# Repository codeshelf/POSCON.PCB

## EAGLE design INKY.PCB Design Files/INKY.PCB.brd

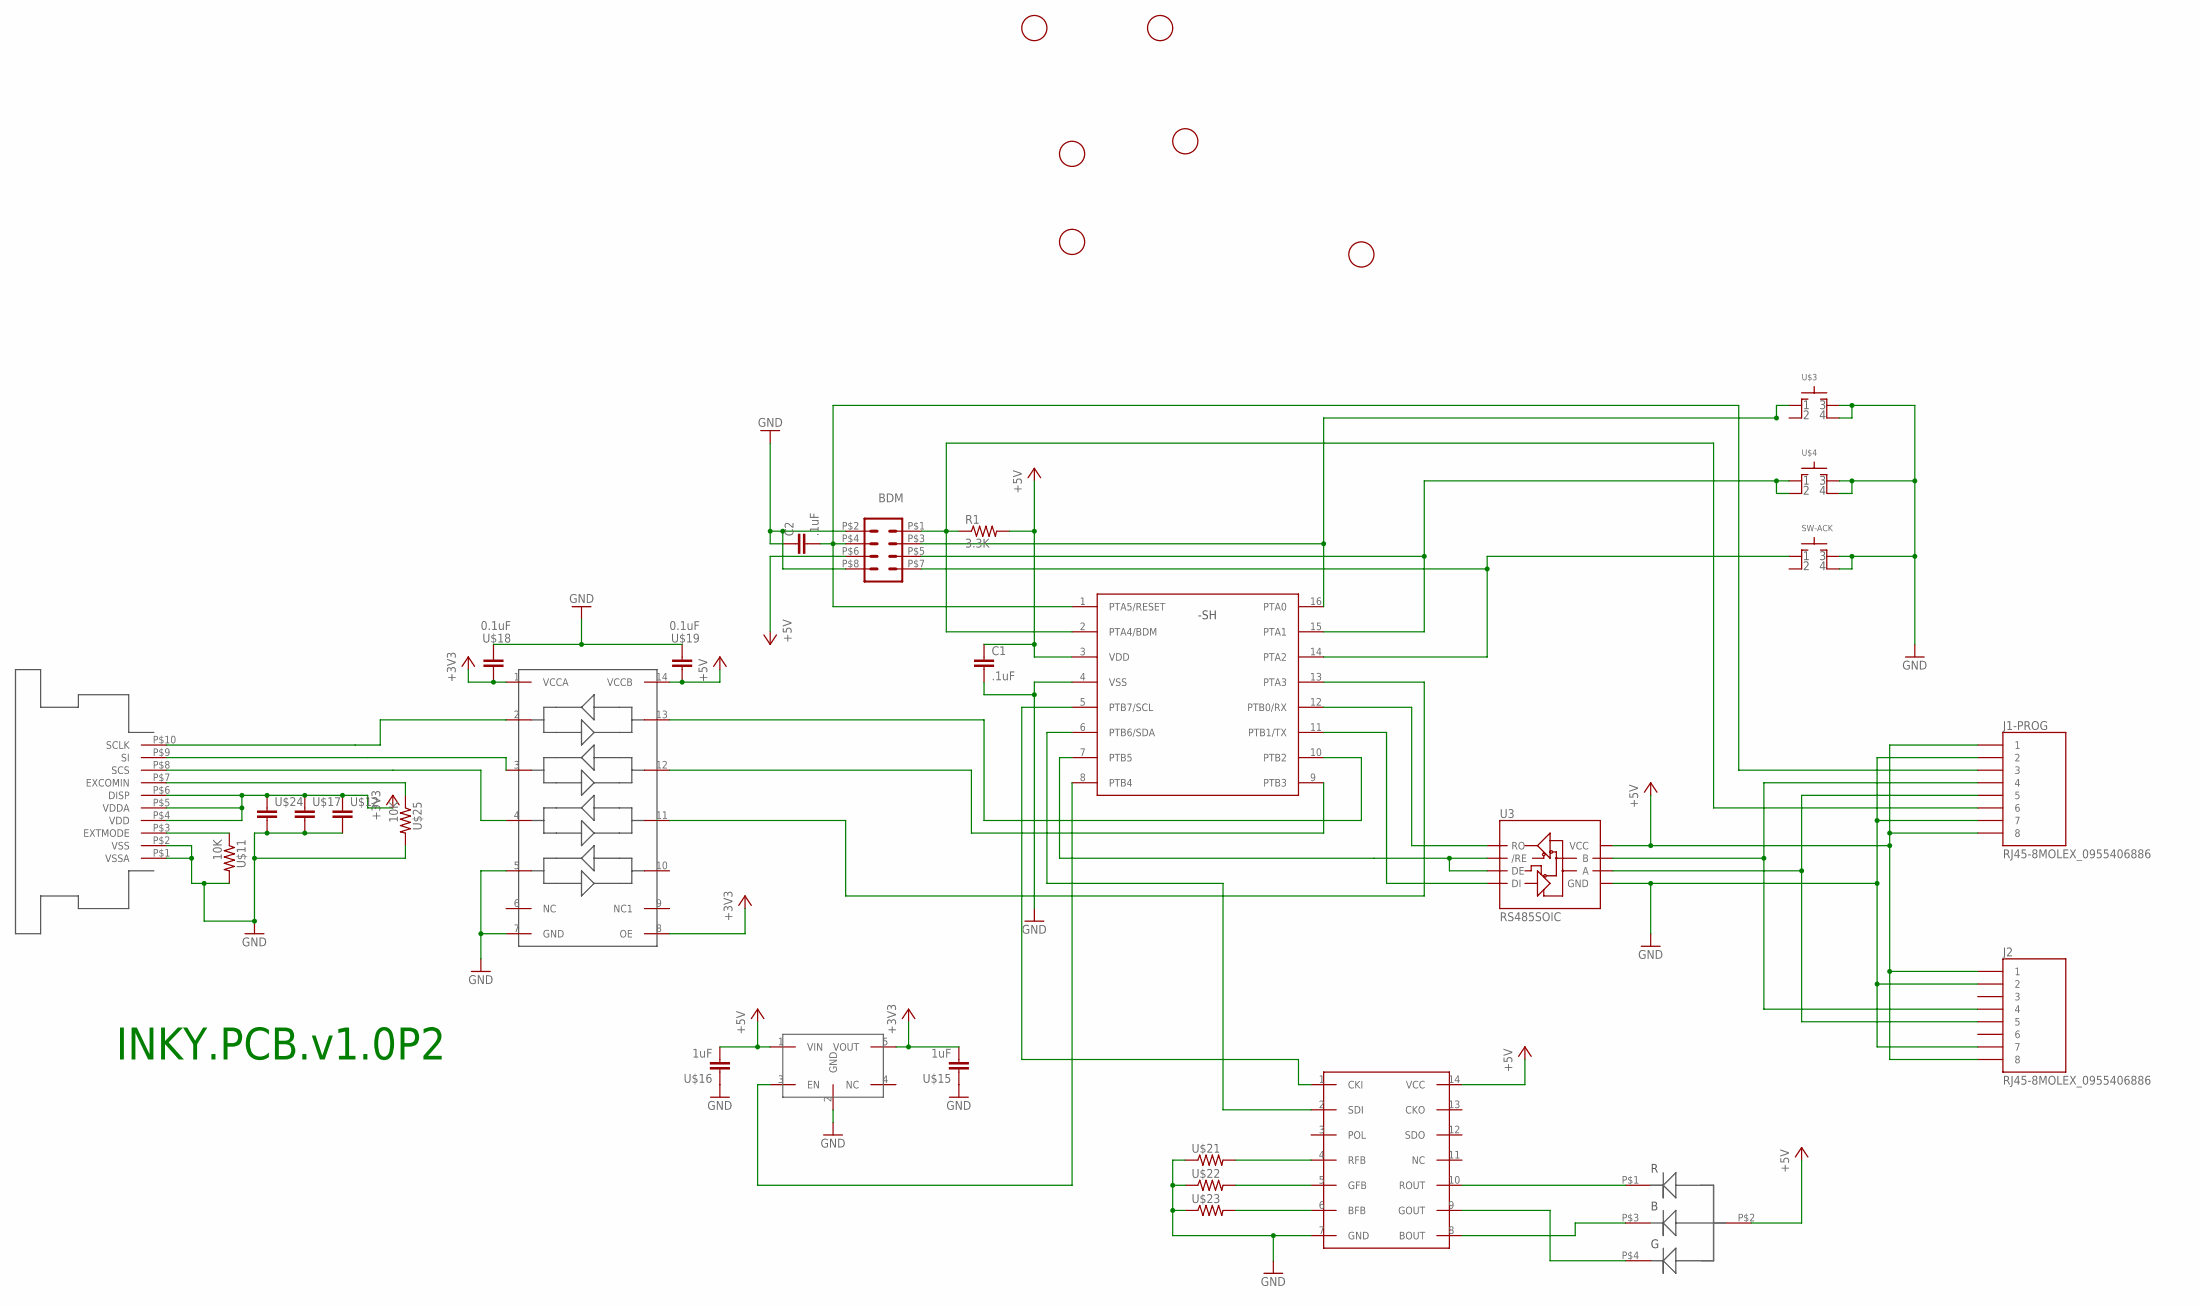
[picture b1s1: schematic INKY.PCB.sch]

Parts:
BDM: TP2X4SMD; SMD4X2
C1, C2: .1uF; C0805
J1-PROG, J2: RJ45-8MOLEX_0955406886; RJ45_GUIDE
R1: 3.3K; RF-C0805
SW-ACK: SWITCH-TACTILE-5E/5GSH9; SWITCH_TACTILE-5E/5GSH9
U1: MC9S08SH8CTG; TSSOP16
U3: RS485SOIC; SO08
U$1, U$2, U$6, U$7, U$8, U$9: FIDUCIAL; FIDUCIAL_1MM
U$3, U$4: SWITCH-TACTILE; ESWITCH-TL3301PF
U$5: WS2801; SO14
U$10: 52745-1097; FPC
U$11, U$25: 10K; RF-C0805
U$12, U$17, U$24: RF-C0805; C0805
U$13: AAT3221IGV-3.3-T1; SOT23-5
U$14: TXB0104; PW_R-PDSO-G14
U$15, U$16: 1uF; C0805
U$18, U$19: 0.1uF; C0805
U$20: RGLBED; PLCC4_SMALL
U$21, U$22, U$23: RF-R0805; RF-C0805

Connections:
485N: J1-PROG.P$4 (4), J2.P$4 (4), U3.7 (B)
485P: J1-PROG.P$5 (5), J2.P$5 (5), U3.6 (A)
+5V: BDM.P$6 (6), C1.1, J1-PROG.P$1 (1), J1-PROG.P$8 (8), J2.P$1 (1), J2.P$8 (8), R1.2, U1.3 (VDD), U3.8 (VCC), U$5.14 (VCC), U$13.1 (VIN), U$14.14 (VCCB), U$16.2, U$19.1, U$20.P$2 (ANODE)
ACK: BDM.P$7 (7), SW-ACK.P$1 (1), U1.14 (PTA2)
BDM: BDM.P$1 (1), J1-PROG.P$6 (6), R1.1, U1.2 (PTA4/BDM)
DIR: U1.7 (PTB5), U3.2 (/RE), U3.3 (DE)
GMD: U$10.P$4 (VDD), U$10.P$5 (VDDA), U$10.P$6 (DISP), U$12.1, U$13.5 (VOUT), U$14.1 (VCCA), U$14.8 (OE), U$15.2, U$17.1, U$18.1, U$24.1
GND: BDM.P$2 (2), BDM.P$8 (8), C1.2, C2.1, J1-PROG.P$2 (2), J1-PROG.P$7 (7), J2.P$2 (2), J2.P$7 (7), SW-ACK.P$3 (3), SW-ACK.P$4 (4), U1.4 (VSS), U3.5 (GND), U$3.3, U$3.4, U$4.3, U$4.4, U$5.7 (GND), U$10.P$1 (VSSA), U$10.P$2 (VSS), U$11.2, U$12.2, U$13.2 (GND), U$14.5, U$14.7 (GND), U$15.1, U$16.1, U$17.2, U$18.2, U$19.2, U$21.1, U$22.1, U$23.1, U$24.2, U$25.2
INC_DOWN: BDM.P$3 (3), U1.16 (PTA0), U$3.1
INC_UP: BDM.P$5 (5), U1.15 (PTA1), U$4.1, U$4.2
unnamed: U1.8 (PTB4), U$13.3 (EN)
unnamed: U$10.P$10 (SCLK), U$14.2
unnamed: U$10.P$9 (SI), U$14.3
unnamed: U$10.P$8 (SCS), U$14.4
unnamed: U1.6 (PTB6/SDA), U$5.2 (SDI)
unnamed: U1.5 (PTB7/SCL), U$5.1 (CKI)
unnamed: U$5.10 (ROUT), U$20.P$1 (RED)
unnamed: U$5.9 (GOUT), U$20.P$4 (GREEN)
unnamed: U$5.8 (BOUT), U$20.P$3 (BLUE)
unnamed: U$5.4 (RFB), U$21.2
unnamed: U$5.5 (GFB), U$22.2
unnamed: U$5.6 (BFB), U$23.2
unnamed: U1.9 (PTB3), U$14.12
unnamed: U1.10 (PTB2), U$14.13
unnamed: U1.13 (PTA3), U$14.11
unnamed: U$10.P$3 (EXTMODE), U$11.1
unnamed: U$10.P$7 (EXCOMIN), U$25.1
RST: BDM.P$4 (4), C2.2, J1-PROG.P$3 (3), U1.1 (PTA5/RESET)
RX: U1.12 (PTB0/RX), U3.1 (RO)
TX: U1.11 (PTB1/TX), U3.4 (DI)

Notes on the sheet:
INKY.PCB.v1.0P2

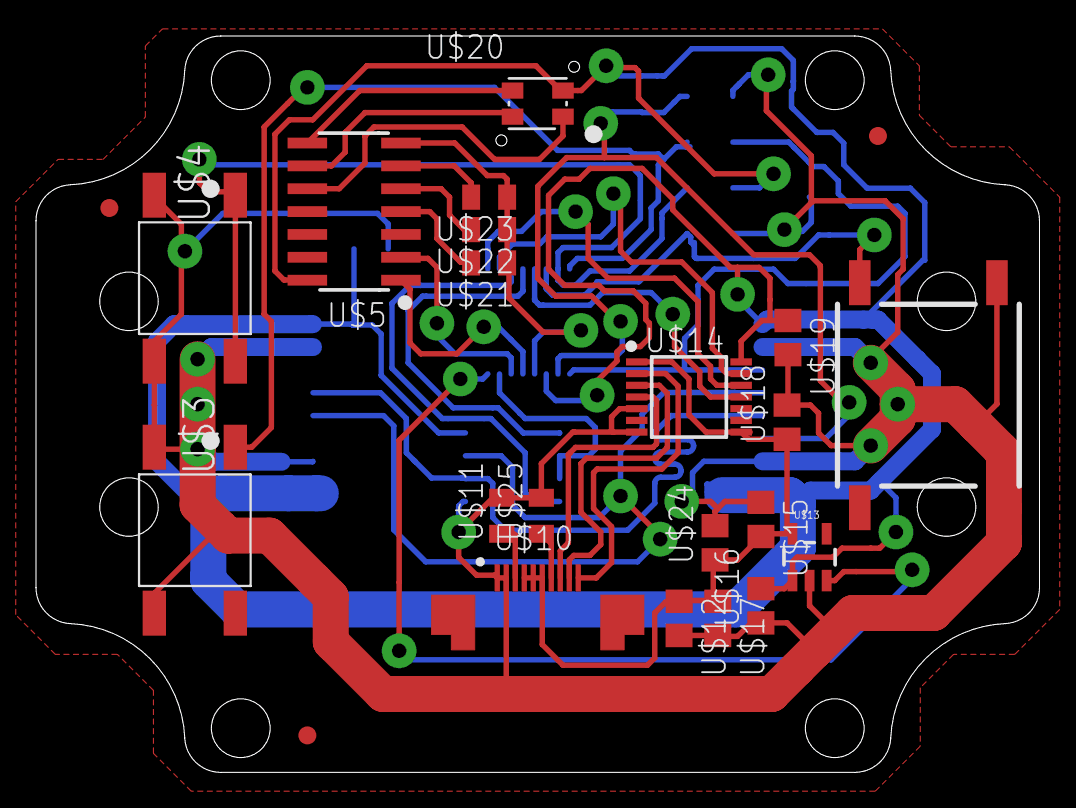
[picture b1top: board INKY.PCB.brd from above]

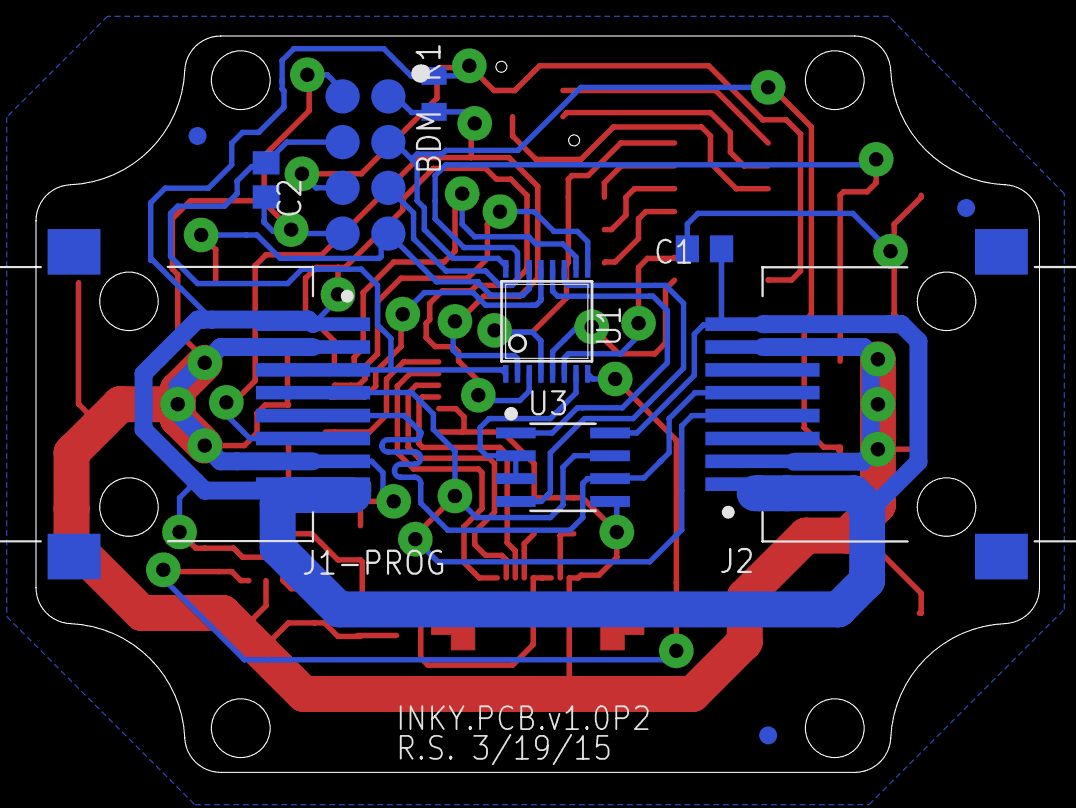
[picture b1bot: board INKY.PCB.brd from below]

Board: 2 copper layers, 55.8 x 40.9 mm, 34 parts (11 on the bottom side), 30 nets.

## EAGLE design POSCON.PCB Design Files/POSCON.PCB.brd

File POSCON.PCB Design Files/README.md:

POSCON.PCB
==========

Position Controller PCB design files (not production files)

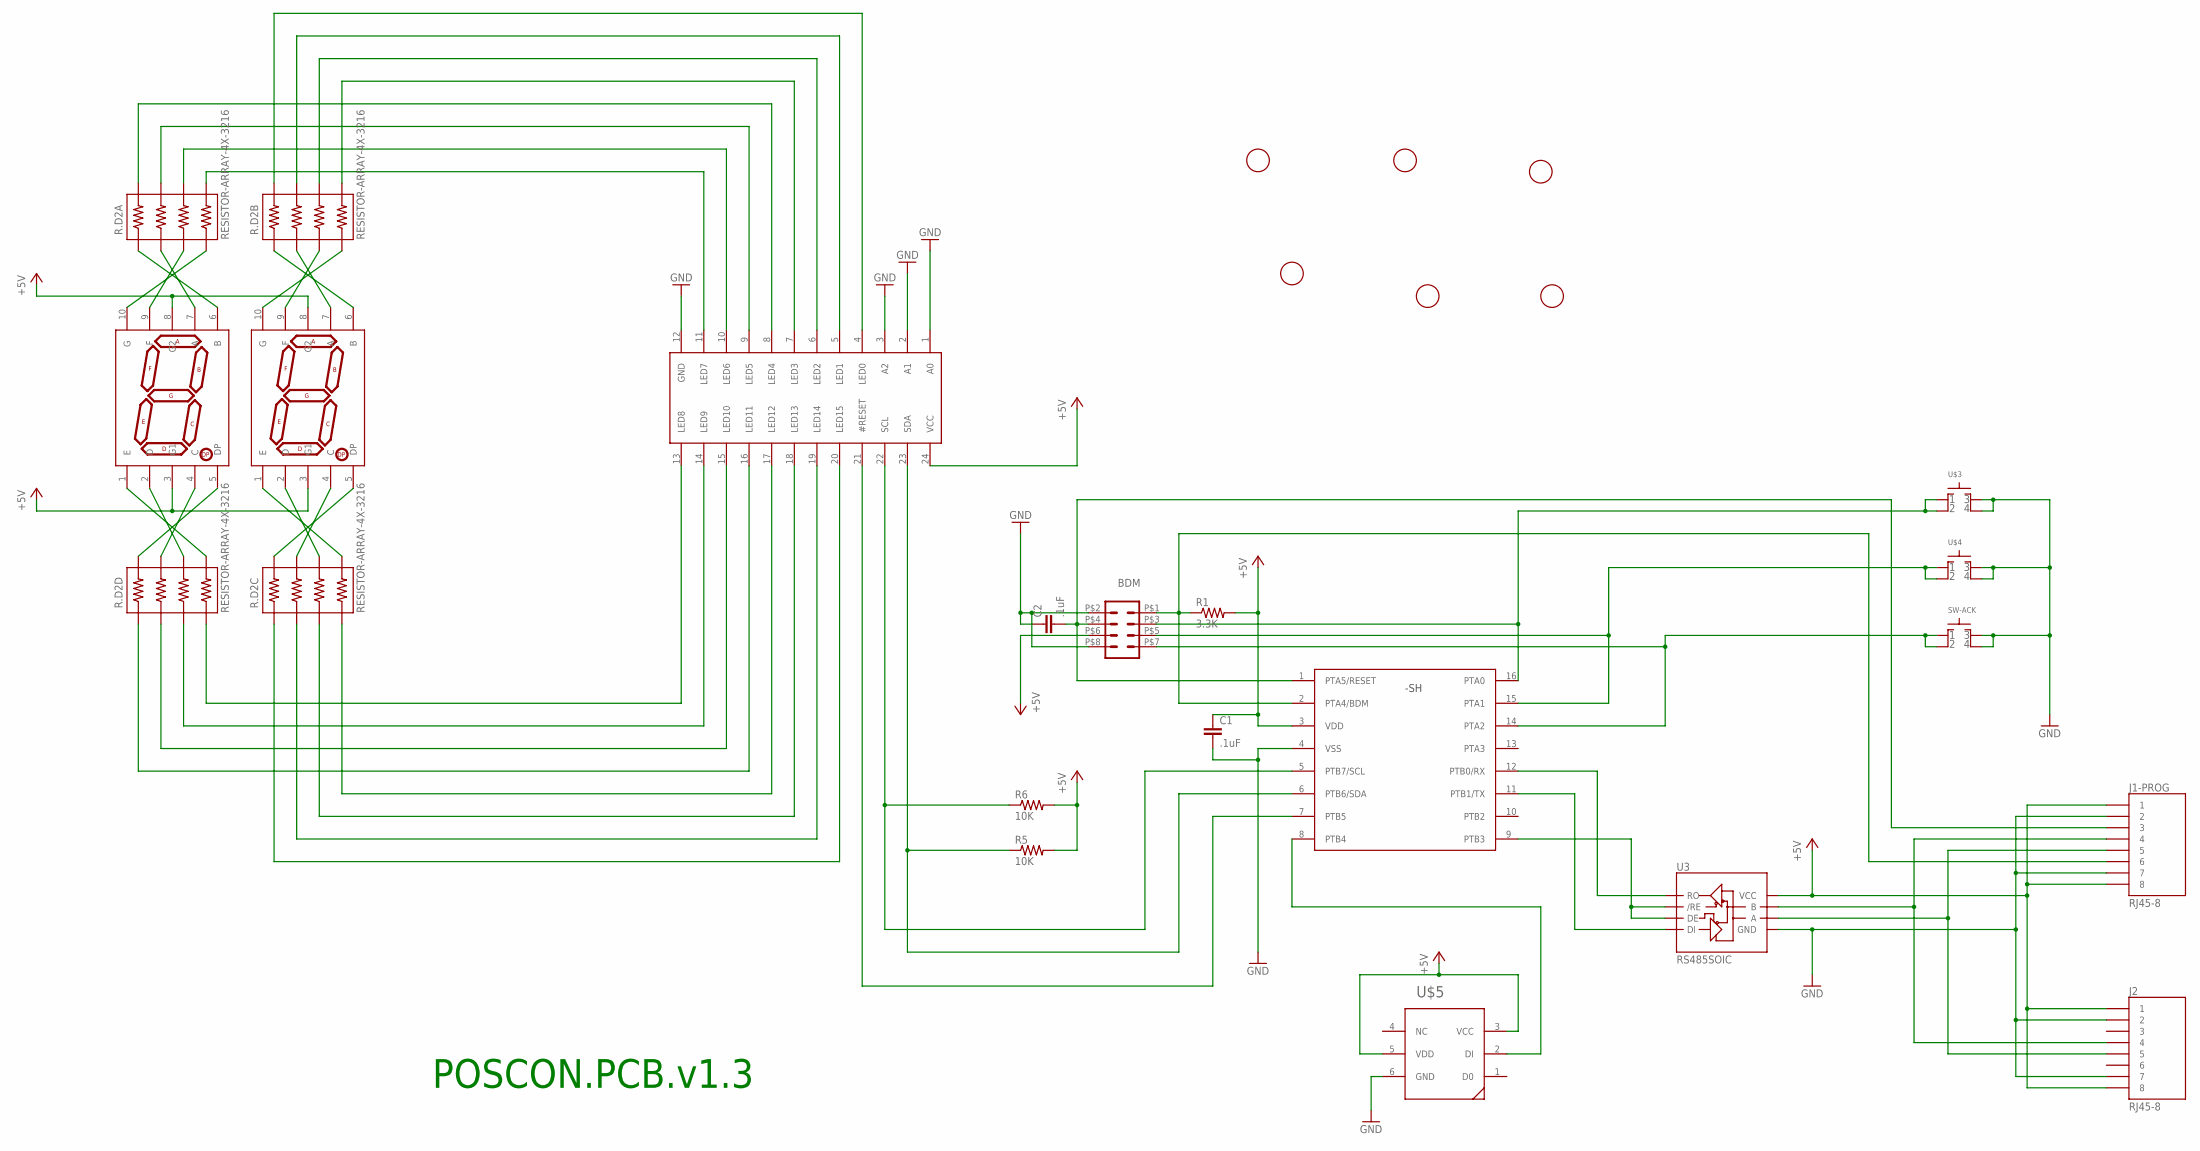
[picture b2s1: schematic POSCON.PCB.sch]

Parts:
BDM: TP2X4SMD; SMD4X2
C1, C2: .1uF; C0402
J1-PROG, J2: RJ45-8; RJ45_SMD
LED1, LED2: 7SEGMENT-1DIGITSMD; 7SEGMENT-1DIG-.40-SMD
R1: 3.3K; RF-R0402
R5, R6: 10K; RF-R0402
R.D2A, R.D2B, R.D2C, R.D2D: RESISTOR-ARRAY-4X-3216; 3216-4X
SW-ACK: SWITCH-TACTILE-320.01E11WHT
U1: MC9S08SH8CTG; TSSOP16
U3: RS485SOIC; SO08
U4: PCA9552; TSSOP24
U$1, U$2, U$6, U$7, U$8, U$9: FIDUCIAL; FIDUCIAL_1MM
U$3, U$4: SWITCH-TACTILE; ESWITCH-TL3301PF
U$5: WS2812; PLCC-6

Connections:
485_N: J1-PROG.P$4 (4), J2.P$4 (4), U3.7 (B)
485_P: J1-PROG.P$5 (5), J2.P$5 (5), U3.6 (A)
+5V: BDM.P$6 (6), C1.1, J1-PROG.P$1 (1), J1-PROG.P$8 (8), J2.P$1 (1), J2.P$8 (8), LED1.3 (G1), LED1.8 (G2), LED2.3 (G1), LED2.8 (G2), R1.2, R5.2, R6.2, U1.3 (VDD), U3.8 (VCC), U4.24 (VCC), U$5.3 (VCC), U$5.5 (VDD)
ACK: BDM.P$7 (7), SW-ACK.P$1 (1), SW-ACK.P$2 (2), U1.14 (PTA2)
BDM: BDM.P$1 (1), J1-PROG.P$6 (6), R1.1, U1.2 (PTA4/BDM)
DIR: U1.9 (PTB3), U3.2 (/RE), U3.3 (DE)
GND: BDM.P$2 (2), BDM.P$8 (8), C1.2, C2.1, J1-PROG.P$2 (2), J1-PROG.P$7 (7), J2.P$2 (2), J2.P$7 (7), SW-ACK.P$3 (3), SW-ACK.P$4 (4), U1.4 (VSS), U3.5 (GND), U4.1 (A0), U4.2 (A1), U4.3 (A2), U4.12 (GND), U$3.3, U$3.4, U$4.3, U$4.4, U$5.6 (GND)
INC_DOWN: BDM.P$3 (3), U1.16 (PTA0), U$3.1, U$3.2
INC_UP: BDM.P$5 (5), U1.15 (PTA1), U$4.1, U$4.2
LED_DI: U1.8 (PTB4), U$5.2 (DI)
unnamed: R.D2A.5 (4B), U4.11 (LED7)
unnamed: R.D2A.6 (3B), U4.10 (LED6)
unnamed: R.D2A.7 (2B), U4.9 (LED5)
unnamed: R.D2A.8 (1B), U4.8 (LED4)
unnamed: R.D2B.5 (4B), U4.7 (LED3)
unnamed: R.D2B.6 (3B), U4.6 (LED2)
unnamed: R.D2B.7 (2B), U4.5 (LED1)
unnamed: R.D2B.8 (1B), U4.4 (LED0)
unnamed: LED2.6 (B), R.D2A.1 (1A)
unnamed: LED2.7 (A), R.D2A.2 (2A)
unnamed: LED2.9 (F), R.D2A.3 (3A)
unnamed: LED2.10 (G), R.D2A.4 (4A)
unnamed: LED2.5 (DP), R.D2D.8 (1B)
unnamed: LED2.4 (C), R.D2D.7 (2B)
unnamed: LED2.2 (D), R.D2D.6 (3B)
unnamed: LED2.1 (E), R.D2D.5 (4B)
unnamed: LED1.6 (B), R.D2B.1 (1A)
unnamed: LED1.7 (A), R.D2B.2 (2A)
unnamed: LED1.9 (F), R.D2B.3 (3A)
unnamed: LED1.10 (G), R.D2B.4 (4A)
unnamed: LED1.5 (DP), R.D2C.8 (1B)
unnamed: R.D2D.4 (4A), U4.13 (LED8)
unnamed: R.D2D.3 (3A), U4.14 (LED9)
unnamed: R.D2D.2 (2A), U4.15 (LED10)
unnamed: R.D2D.1 (1A), U4.16 (LED11)
unnamed: R.D2C.4 (4A), U4.17 (LED12)
unnamed: R.D2C.3 (3A), U4.18 (LED13)
unnamed: R.D2C.2 (2A), U4.19 (LED14)
unnamed: R.D2C.1 (1A), U4.20 (LED15)
unnamed: LED1.4 (C), R.D2C.7 (2B)
unnamed: LED1.2 (D), R.D2C.6 (3B)
unnamed: LED1.1 (E), R.D2C.5 (4B)
RESET: U1.7 (PTB5), U4.21 (#RESET)
RST: BDM.P$4 (4), C2.2, J1-PROG.P$3 (3), U1.1 (PTA5/RESET)
RX: U1.12 (PTB0/RX), U3.1 (RO)
SCL: R6.1, U1.5 (PTB7/SCL), U4.22 (SCL)
SDA: R5.1, U1.6 (PTB6/SDA), U4.23 (SDA)
TX: U1.11 (PTB1/TX), U3.4 (DI)

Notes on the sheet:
POSCON.PCB.v1.3

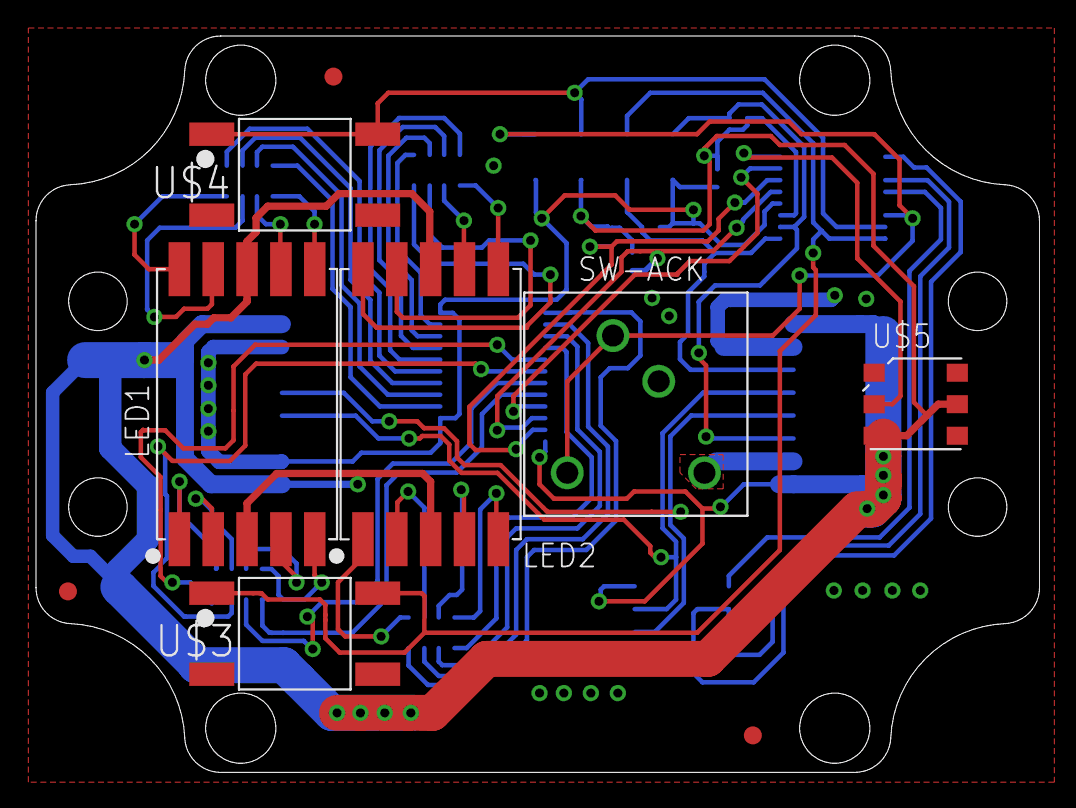
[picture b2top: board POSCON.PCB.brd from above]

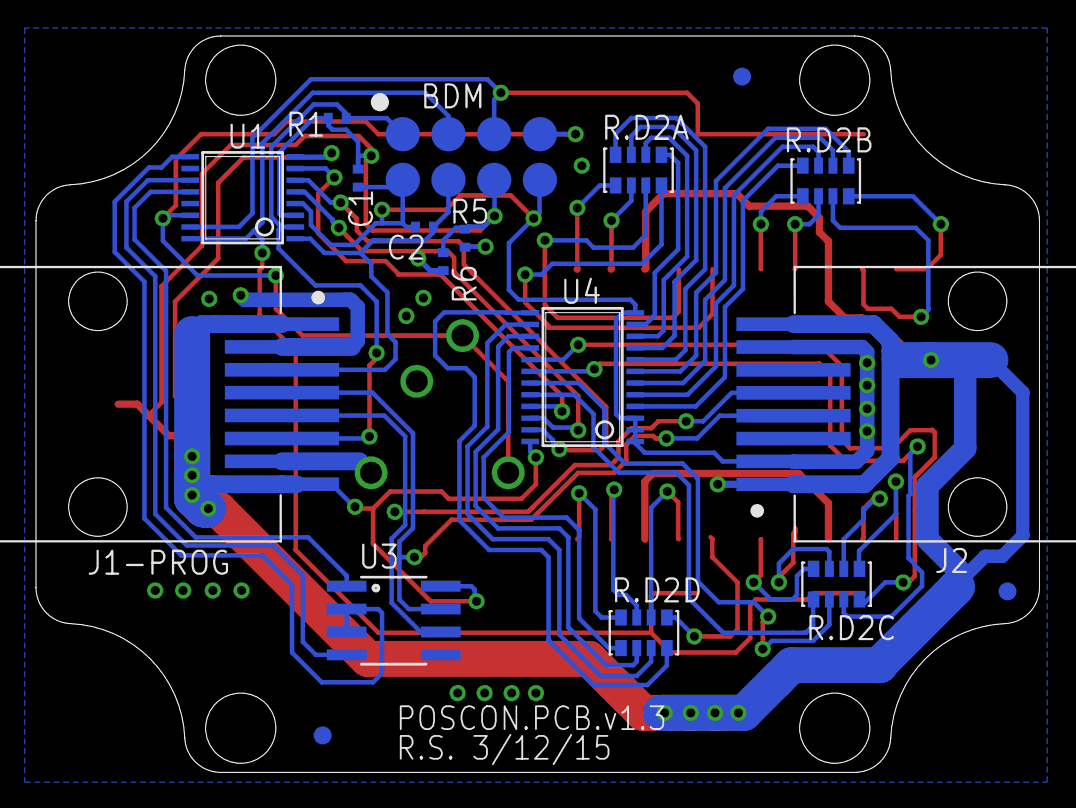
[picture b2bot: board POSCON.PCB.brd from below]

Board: 2 copper layers, 55.8 x 40.9 mm, 27 parts (18 on the bottom side), 48 nets.

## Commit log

2014-10-10 Imported files from Archive repo
    Moved POSCON design files from Archive/POSCON.PCB repo
2014-10-13 Added .gitignore
2014-10-14 Added PCB.ECO
    Added PCB.ECO file. This will be first version
2014-10-14 POSCON.PCB.v1.0
    Release version. Moved Gerbers to top level (no production files here!).
    Added version name to bottom silk
2014-10-15 Added production files
    Moved production files back into this repo
2014-10-22 Files moved, PCB.v1.1
    Consolidated more files. This is tag v1.1. No design changes from v1.0
    (which is being produced).
2014-12-20 Fixing power traces in progress
    Not done. Moved components
2014-12-31 Finished power trace
    Changed label to v1.1, fixed traces and moved vias / traces to
    accomodate
2015-01-07 Prepare for release 1.2
    Labelling, part names and numbers, new Gerbers and production documents
2015-01-10 Fixing DRC
    Residual Eagle errors on checklist
2015-01-10 New files for release 1.2
    For review and sent to quote at AC.
2015-01-13 Release v1.2
    Moved zip file to top level.
2015-01-28 Inky routing
    75% Inky routing
2015-01-29 Still routing
    ~ 95% done
2015-02-26 Inky finishing
    Done routing, need to fix angles.
2015-03-03 Inky v0.1
2015-03-13 Release v1.3
    Fixed silkscreen (pin 1 markers), added WS2812S, added date / name to
    fab text and updated all files correspondingly (BOM, ECO)
2015-03-19 Inky 0.2
2015-03-19 Inky.PCB.v1.0P2
    Updated date
